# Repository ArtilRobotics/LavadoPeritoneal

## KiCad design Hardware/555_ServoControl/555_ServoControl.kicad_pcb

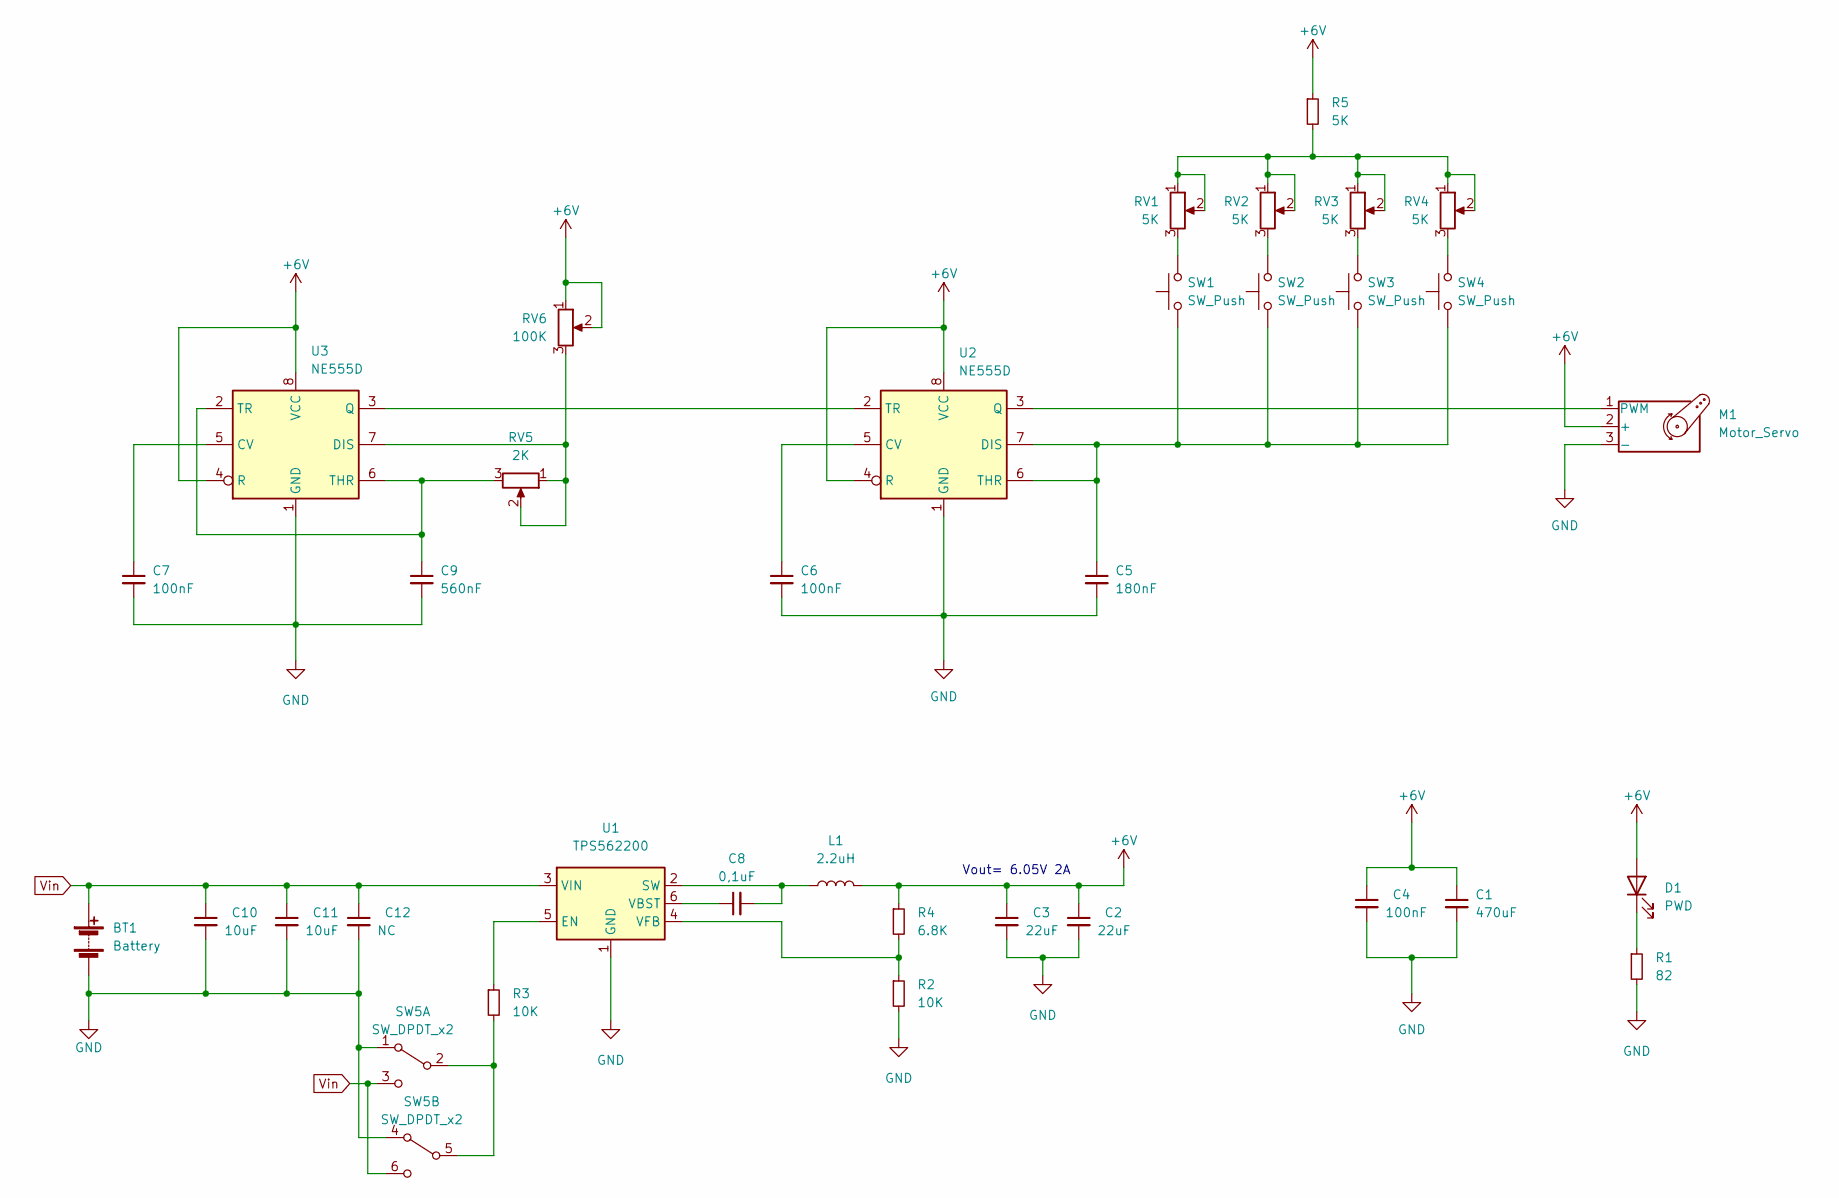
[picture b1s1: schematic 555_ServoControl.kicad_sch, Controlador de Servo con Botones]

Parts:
BT1: Battery; BatteryHolder_Eagle_12BH611-GR
C1: 470uF; CP_Elec_6.3x7.7; LCSC C335982
C2, C3: 22uF; C_0402_1005Metric; LCSC C1525
C4, C6, C7: 100nF; C_0402_1005Metric; LCSC C2857965
C5: 180nF; C_0402_1005Metric; LCSC C458937
C8: 0,1uF; C_0402_1005Metric
C9: 560nF; C_1206_3216Metric; LCSC C717022
C10, C11: 10uF; C_0402_1005Metric; LCSC C13585
C12: NC; C_0402_1005Metric; LCSC C13585
D1: PWD; LED_0805_2012Metric
L1: 2.2uH; L_Wuerth_WE-GF-1210; LCSC C98016
M1: Motor_Servo; PinHeader_1x03_P2.54mm_Horizontal; LCSC C92159
R1: 82; R_0402_1005Metric
R2, R3: 10K; R_0402_1005Metric; LCSC C60490
R4: 6.8K; R_0402_1005Metric; LCSC C114632
R5: 5K; R_0402_1005Metric; LCSC C60490
RV1, RV2, RV3, RV4: 5K; POT; LCSC C118903
RV5: 2K; POT; LCSC C118929
RV6: 100K; POT; LCSC C118966
SW1, SW2, SW3, SW4: SW_Push; SW_SPST_PTS645; LCSC C285468
SW5: SW_DPDT_x2; SW_E-Switch_EG1271_DPDT; LCSC C273396
U1: TPS562200; SOT-23-6; LCSC C49757
U2, U3: NE555D; SOIC-8_3.9x4.9mm_P1.27mm; LCSC C7593

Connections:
+6V: C1.1, C2.1, C3.1, C4.1, D1.2 (A), L1.2, M1.2 (+), R4.1, R5.1, RV6.1, RV6.2, U2.4 (R), U2.8 (VCC), U3.4 (R), U3.8 (VCC)
GND: BT1.2 (-), C1.2, C2.2, C3.2, C4.2, C5.2, C6.2, C7.2, C9.2, C10.2, C11.2, C12.2, M1.3 (-), R1.2, R2.2, SW5.1 (A), SW5.4 (A), U1.1 (GND), U2.1 (GND), U3.1 (GND)
unnamed: C9.1, RV5.3, U3.2 (TR), U3.6 (THR)
unnamed: C8.1, U1.6 (VBST)
unnamed: C8.2, L1.1, U1.2 (SW)
unnamed: C5.1, SW1.1, SW2.1, SW3.1, SW4.1, U2.6 (THR), U2.7 (DIS)
unnamed: C6.1, U2.5 (CV)
unnamed: C7.1, U3.5 (CV)
unnamed: D1.1 (K), R1.1
unnamed: M1.1 (PWM), U2.3 (Q)
unnamed: R3.1, U1.5 (EN)
unnamed: R3.2, SW5.2 (B), SW5.5 (B)
unnamed: R5.2, RV1.1, RV1.2, RV2.1, RV2.2, RV3.1, RV3.2, RV4.1, RV4.2
unnamed: R2.1, R4.2, U1.4 (VFB)
unnamed: RV1.3, SW1.2
unnamed: RV2.3, SW2.2
unnamed: RV4.3, SW4.2
unnamed: RV3.3, SW3.2
unnamed: RV5.1, RV5.2, RV6.3, U3.7 (DIS)
unnamed: U2.2 (TR), U3.3 (Q)
Vin: BT1.1 (+), C10.1, C11.1, C12.1, SW5.3 (C), SW5.6 (C), U1.3 (VIN)

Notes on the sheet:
Vout= 6.05V 2A

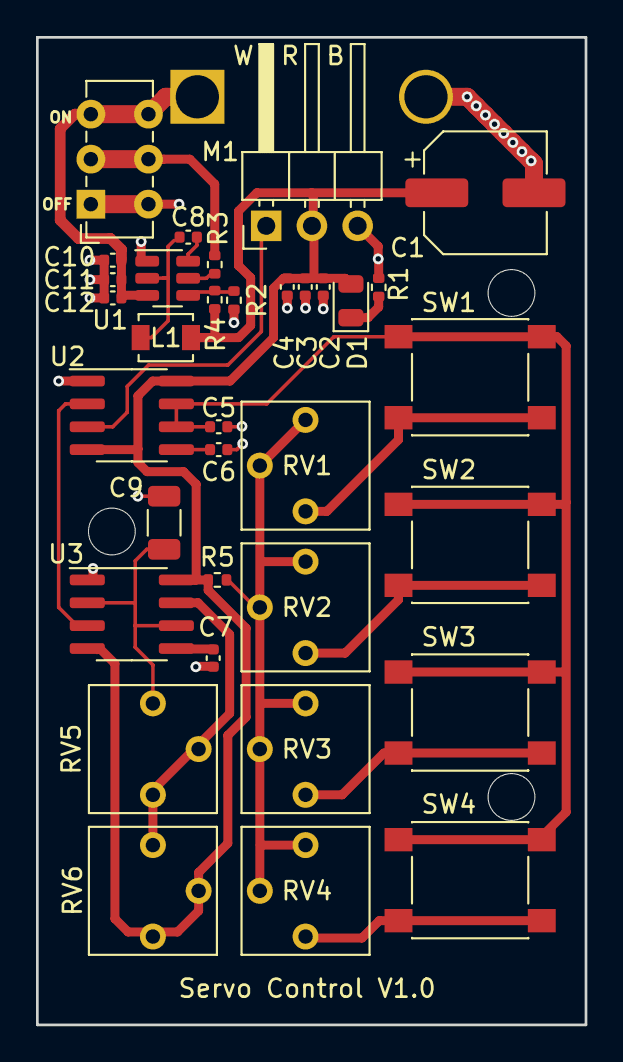
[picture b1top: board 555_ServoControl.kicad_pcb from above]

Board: 2 copper layers, 30.5 x 54.9 mm, 35 parts (1 on the bottom side), 21 nets.

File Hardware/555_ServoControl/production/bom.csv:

Designator,Footprint,Quantity,Value,LCSC Part #
BT1,BatteryHolder_Eagle_12BH611-GR,1,Battery,
C1,CP_Elec_6.3x7.7,1,470uF,C335982
"C10, C11",C_0402_1005Metric,2,10uF,C13585
C12,C_0402_1005Metric,1,NC,C13585
"C2, C3",C_0402_1005Metric,2,22uF,C1525
"C4, C6, C7",C_0402_1005Metric,3,100nF,C2857965
C5,C_0402_1005Metric,1,180nF,C458937
C8,C_0402_1005Metric,1,"0,1uF",
C9,C_1206_3216Metric,1,560nF,C717022
D1,LED_0805_2012Metric,1,PWD,
L1,L_Wuerth_WE-GF-1210,1,2.2uH,C98016
M1,PinHeader_1x03_P2.54mm_Horizontal,1,Motor_Servo,C92159
R1,R_0402_1005Metric,1,82,
"R2, R3",R_0402_1005Metric,2,10K,C60490
R4,R_0402_1005Metric,1,6.8K,C114632
R5,R_0402_1005Metric,1,5K,C60490
"RV1, RV2, RV3, RV4",POT,4,5K,C118903
RV5,POT,1,2K,C118929
RV6,POT,1,100K,C118966
"SW1, SW2, SW3, SW4",SW_SPST_PTS645,4,SW_Push,C285468
SW5,SW_E-Switch_EG1271_DPDT,1,SW_DPDT_x2,C273396
U1,SOT-23-6,1,TPS562200,C49757
"U2, U3",SOIC-8_3.9x4.9mm_P1.27mm,2,NE555D,C7593

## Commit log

2022-09-14 Version con PullUps
2022-09-14 Agragar archivo Hola
2022-09-14 Aumento de robustes ante mal uso con la fun millis
2022-09-15 Mejorar robustez usando funcion millis
2023-01-26 New board with 555
